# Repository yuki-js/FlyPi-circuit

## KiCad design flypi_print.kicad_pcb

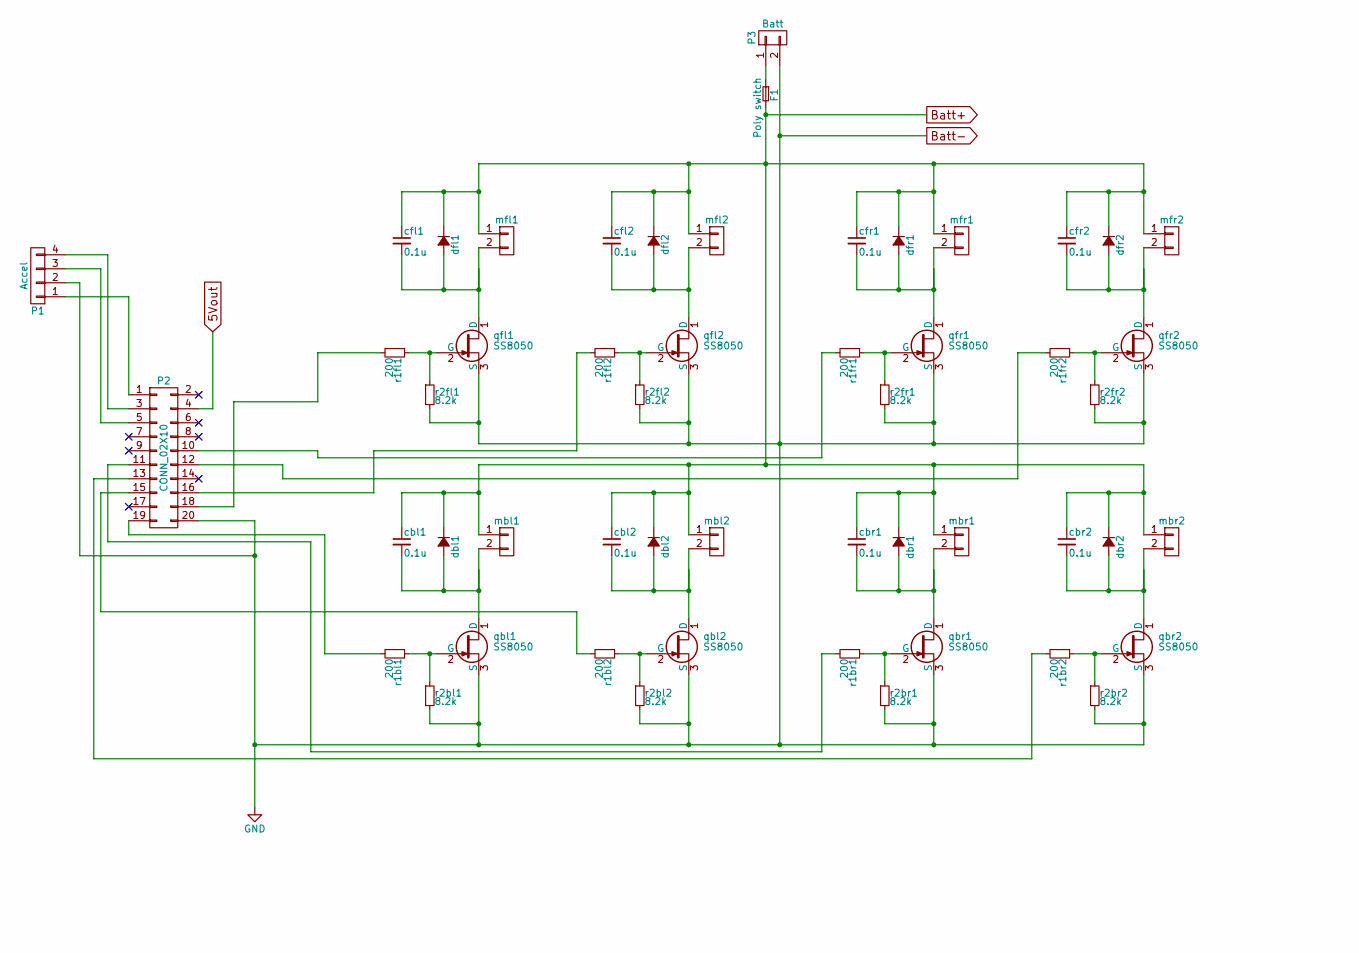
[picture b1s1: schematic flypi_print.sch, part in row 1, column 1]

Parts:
F1: Poly switch; polysw
P1: Accel; Pin_Header_Straight_1x04_Pitch2.54mm
P2: CONN_02X10; Pin_Header_Straight_2x10_Pitch2.54mm
P3: Batt; Pin_Header_Straight_1x02_Pitch2.54mm
cbl1, cbl2: 0.1u; C_1210_HandSoldering
cbr1, cbr2: 0.1u; C_1210_HandSoldering
cfl1, cfl2: 0.1u; C_1210_HandSoldering
cfr1, cfr2: 0.1u; C_1210_HandSoldering
dbl1, dbl2: D_Small; D_SOD-123F
dbr1, dbr2: D_Small; D_SOD-123F
dfl1, dfl2: D_Small; D_SOD-123F
dfr1, dfr2: D_Small; D_SOD-123F
mbl1: mbl1; Pin_Header_Straight_2x01_Pitch2.54mm
mbl2: mbl2; Pin_Header_Straight_2x01_Pitch2.54mm
mbr1: mbr1; Pin_Header_Straight_2x01_Pitch2.54mm
mbr2: mbr2; Pin_Header_Straight_2x01_Pitch2.54mm
mfl1, mfl2: CONN_01X02; Pin_Header_Straight_2x01_Pitch2.54mm
mfr1, mfr2: CONN_01X02; Pin_Header_Straight_2x01_Pitch2.54mm
qbl1, qbl2: SS8050; SPN3414S23RGB
qbr1, qbr2: SS8050; SPN3414S23RGB
qfl1, qfl2: SS8050; SPN3414S23RGB
qfr1, qfr2: SS8050; SPN3414S23RGB
r1bl1, r1bl2, r1br1, r1br2, r1fl1, r1fl2, r1fr1, r1fr2: 200; R_1206_HandSoldering
r2bl1, r2bl2, r2br1, r2br2, r2fl1, r2fl2, r2fr1, r2fr2: 8.2k; R_1206_HandSoldering

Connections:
5Vout: P2.4; also elsewhere on the board
Batt+: F1.2, cbl1.1, cbl2.1, cbr1.1, cbr2.1, cfl1.1, cfl2.1, cfr1.1, cfr2.1, dbl1.1 (K), dbl2.1 (K), dbr1.1 (K), dbr2.1 (K), dfl1.1 (K), dfl2.1 (K), dfr1.1 (K), dfr2.1 (K), mbl1.1, mbl2.1, mbr1.1, mbr2.1, mfl1.1, mfl2.1, mfr1.1, mfr2.1; also elsewhere on the board
Batt-: P1.2, P2.20, P3.2, qbl1.3 (S), qbl2.3 (S), qbr1.3 (S), qbr2.3 (S), qfl1.3 (S), qfl2.3 (S), qfr1.3 (S), qfr2.3 (S), r2bl1.2, r2bl2.2, r2br1.2, r2br2.2, r2fl1.2, r2fl2.2, r2fr1.2, r2fr2.2; also elsewhere on the board
unnamed: F1.1, P3.1
unnamed: P1.1, P2.1
unnamed: P1.3, P2.5
unnamed: P1.4, P2.3
unnamed: P2.10, r1fr1.2
unnamed: P2.11, r1br1.2
unnamed: P2.12, r1fr2.2
unnamed: P2.13, r1br2.2
unnamed: P2.15, r1bl2.2
unnamed: P2.16, r1fl2.2
unnamed: P2.18, r1fl1.2
unnamed: P2.19, r1bl1.2
unnamed: cbl1.2, dbl1.2 (A), mbl1.2, qbl1.1 (D)
unnamed: cbl2.2, dbl2.2 (A), mbl2.2, qbl2.1 (D)
unnamed: cbr1.2, dbr1.2 (A), mbr1.2, qbr1.1 (D)
unnamed: cbr2.2, dbr2.2 (A), mbr2.2, qbr2.1 (D)
unnamed: cfl1.2, dfl1.2 (A), mfl1.2, qfl1.1 (D)
unnamed: cfl2.2, dfl2.2 (A), mfl2.2, qfl2.1 (D)
unnamed: cfr1.2, dfr1.2 (A), mfr1.2, qfr1.1 (D)
unnamed: cfr2.2, dfr2.2 (A), mfr2.2, qfr2.1 (D)
unnamed: qbl1.2 (G), r1bl1.1, r2bl1.1
unnamed: qbl2.2 (G), r1bl2.1, r2bl2.1
unnamed: qbr1.2 (G), r1br1.1, r2br1.1
unnamed: qbr2.2 (G), r1br2.1, r2br2.1
unnamed: qfl1.2 (G), r1fl1.1, r2fl1.1
unnamed: qfl2.2 (G), r1fl2.1, r2fl2.1
unnamed: qfr1.2 (G), r1fr1.1, r2fr1.1
unnamed: qfr2.2 (G), r1fr2.1, r2fr2.1

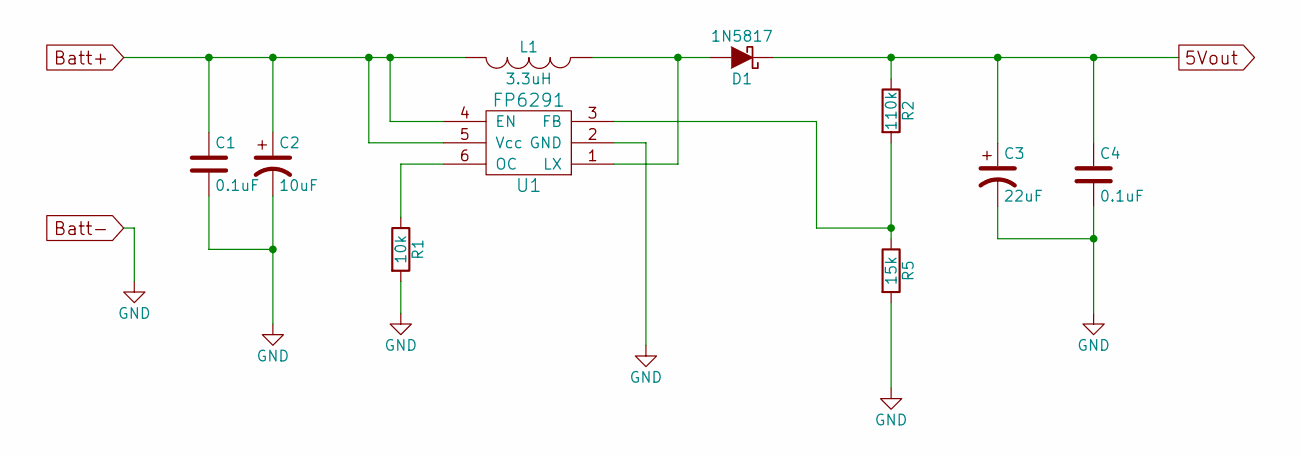
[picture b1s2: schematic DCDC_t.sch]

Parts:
C1, C4: 0.1uF; C_1210_HandSoldering
C2: 10uF; C_1210_HandSoldering
C3: 22uF; C_0805_HandSoldering
D1: 1N5817; D_SOD-123F
L1: 3.3uH; SELF-WE-PD-XXL
R1: 10k; R_1206_HandSoldering
R2: 110k; R_1206_HandSoldering
R5: 15k; R_1206_HandSoldering
U1: FP6291

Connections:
5Vout: C3.1, C4.1, D1.1 (K), R2.1; also elsewhere on the board
Batt+: C1.1, C2.1, L1.2, U1.4 (EN), U1.5 (Vcc); also elsewhere on the board
Batt-: C1.2, C2.2, C3.2, C4.2, R1.2, R5.2, U1.2 (GND); also elsewhere on the board
unnamed: D1.2 (A), L1.1, U1.1 (LX)
unnamed: R1.1, U1.6 (OC)
unnamed: R2.2, R5.1, U1.3 (FB)

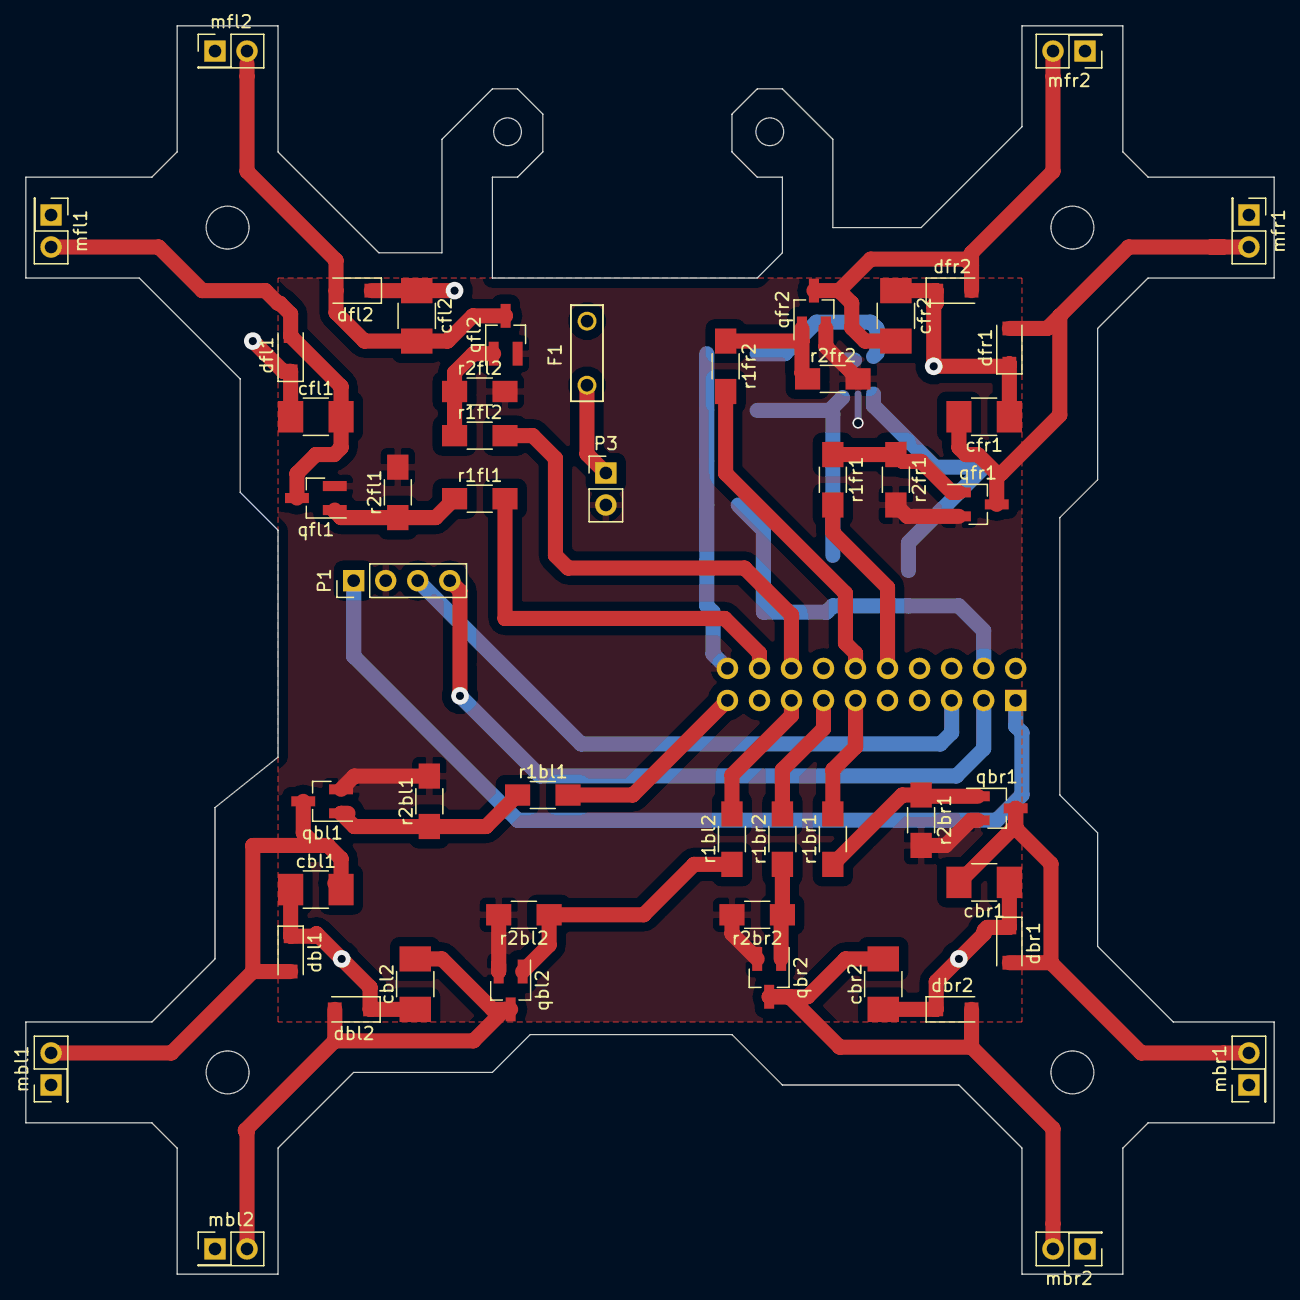
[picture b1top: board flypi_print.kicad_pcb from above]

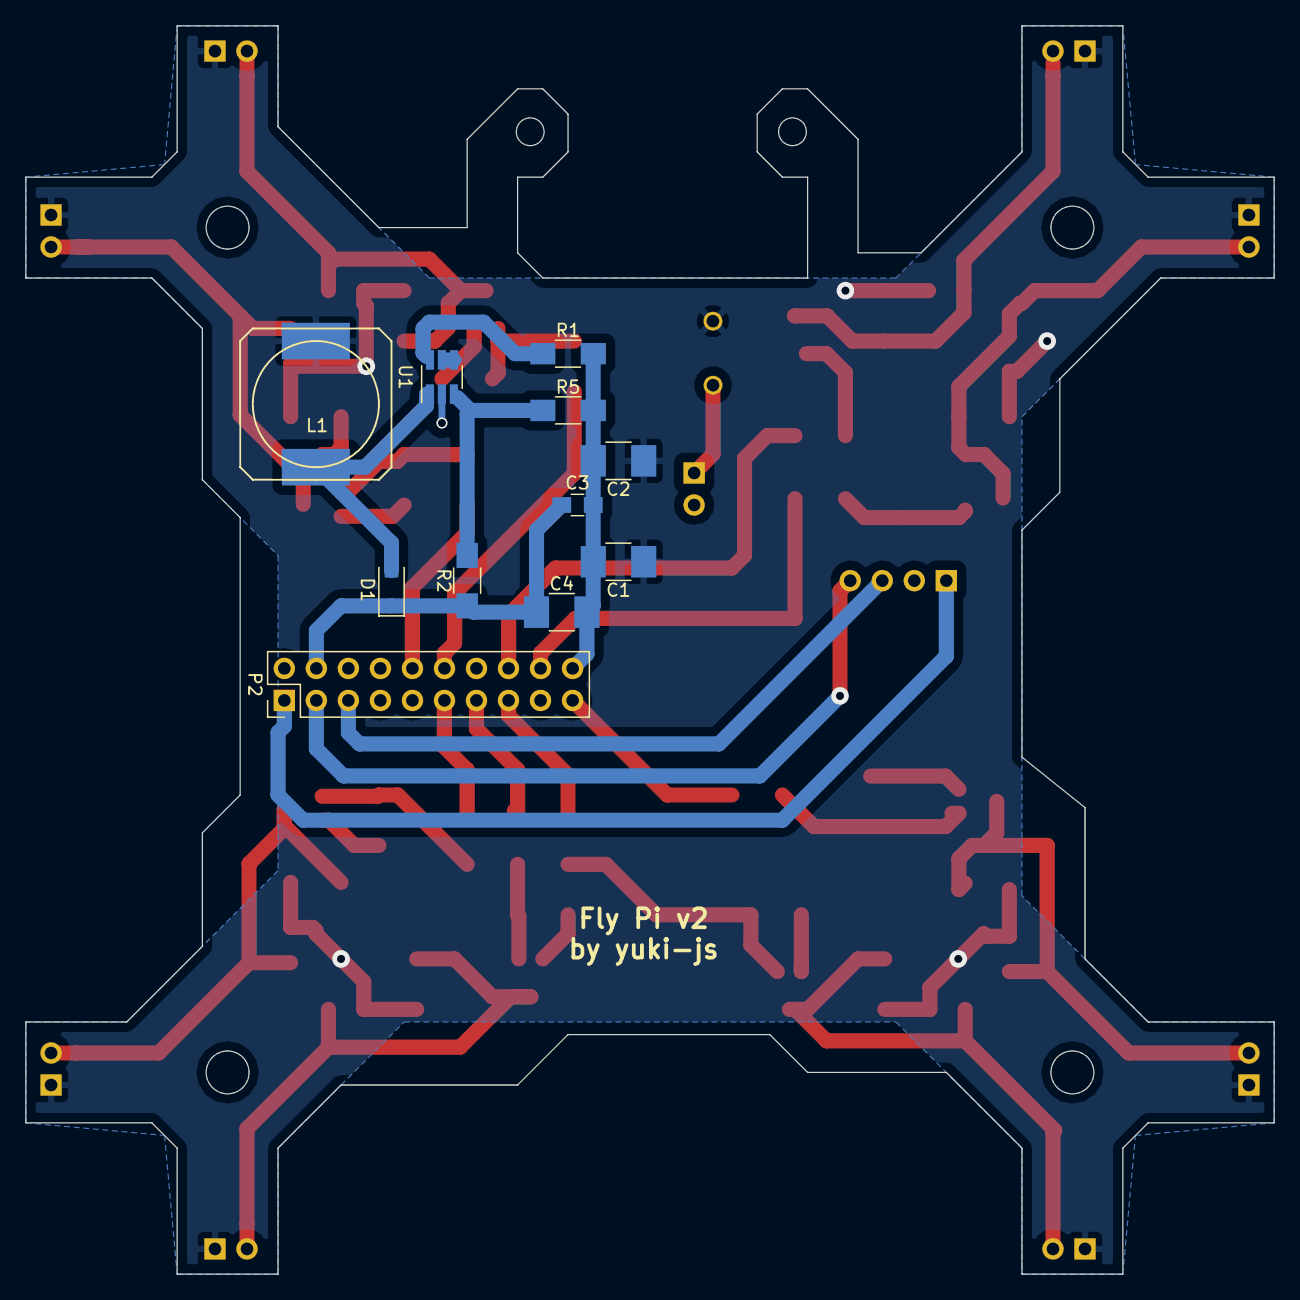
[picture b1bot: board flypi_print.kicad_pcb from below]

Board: 2 copper layers, 99.0 x 99.0 mm, 62 parts (11 on the bottom side), 34 nets.
